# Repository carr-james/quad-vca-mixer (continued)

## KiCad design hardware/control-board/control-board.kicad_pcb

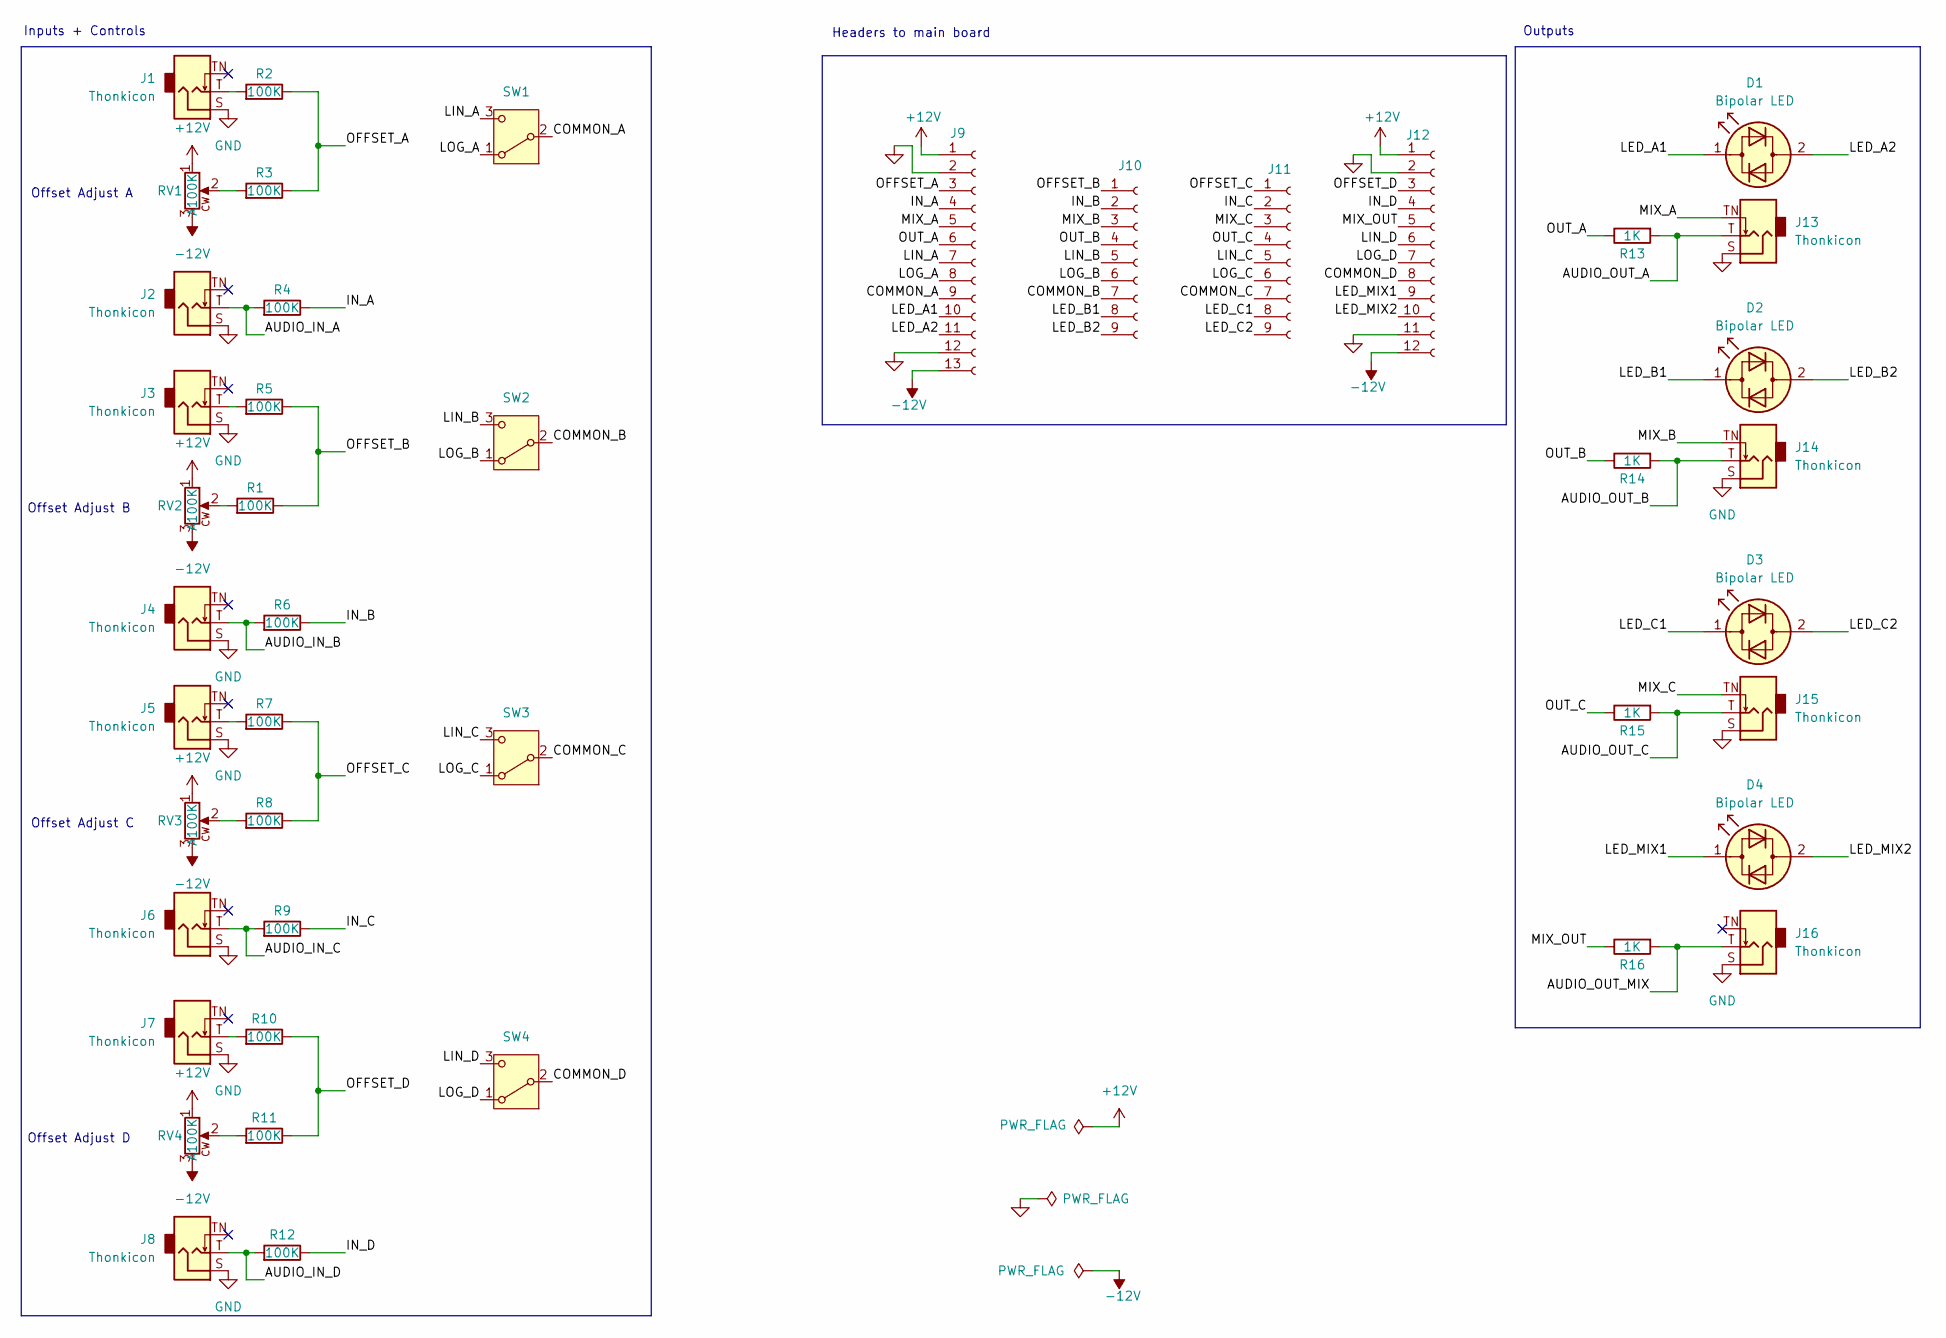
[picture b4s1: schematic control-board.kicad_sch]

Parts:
D1, D2, D3, D4: Bipolar LED; LED_D3.0mm
J1, J2, J3, J4, J5, J6, J7, J8, J13, J14, J15, J16: Thonkicon
J9: 01x13 Male Pin Header; PinHeader_1x13_P2.54mm_Vertical
J10, J11: 01x09 Male Pin Header; PinHeader_1x09_P2.54mm_Vertical
J12: 01x12 Male Pin Header; PinHeader_1x12_P2.54mm_Vertical
R1, R2, R3, R4, R5, R6, R7, R8, R9, R10, R11, R12: 100K; R_Axial_DIN0207_L6.3mm_D2.5mm_P7.62mm_Horizontal
R13, R14, R15, R16: 1K; R_Axial_DIN0207_L6.3mm_D2.5mm_P7.62mm_Horizontal
RV1, RV2, RV3, RV4: A100K; Alpha Potentiometer
SW1, SW2, SW3, SW4: Subminiture SPDT; Sub-Miniature SPDT

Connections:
+12V: J9.1, J12.1, RV1.1, RV2.1, RV3.1, RV4.1
-12V: J9.13, J12.12, RV1.3, RV2.3, RV3.3, RV4.3
/AUDIO_IN_A: J2.T, R4.1
/AUDIO_IN_B: J4.T, R6.1
/AUDIO_IN_C: J6.T, R9.1
/AUDIO_IN_D: J8.T, R12.1
/AUDIO_OUT_A: J13.T, R13.1
/AUDIO_OUT_B: J14.T, R14.1
/AUDIO_OUT_C: J15.T, R15.1
/AUDIO_OUT_MIX: J16.T, R16.1
/COMMON_A: J9.9, SW1.2 (B)
/COMMON_B: J10.7, SW2.2 (B)
/COMMON_C: J11.7, SW3.2 (B)
/COMMON_D: J12.8, SW4.2 (B)
/IN_A: J9.4, R4.2
/IN_B: J10.2, R6.2
/IN_C: J11.2, R9.2
/IN_D: J12.4, R12.2
/LED_A1: D1.1 (KA), J9.10
/LED_A2: D1.2 (AK), J9.11
/LED_B1: D2.1 (KA), J10.8
/LED_B2: D2.2 (AK), J10.9
/LED_C1: D3.1 (KA), J11.8
/LED_C2: D3.2 (AK), J11.9
/LED_MIX1: D4.1 (KA), J12.9
/LED_MIX2: D4.2 (AK), J12.10
/LIN_A: J9.7, SW1.3 (C)
/LIN_B: J10.5, SW2.3 (C)
/LIN_C: J11.5, SW3.3 (C)
/LIN_D: J12.6, SW4.3 (C)
/LOG_A: J9.8, SW1.1 (A)
/LOG_B: J10.6, SW2.1 (A)
/LOG_C: J11.6, SW3.1 (A)
/LOG_D: J12.7, SW4.1 (A)
/MIX_A: J9.5, J13.TN
/MIX_B: J10.3, J14.TN
/MIX_C: J11.3, J15.TN
/MIX_OUT: J12.5, R16.2
/OFFSET_A: J9.3, R2.2, R3.2
/OFFSET_B: J10.1, R1.2, R5.2
/OFFSET_C: J11.1, R7.2, R8.2
/OFFSET_D: J12.3, R10.2, R11.2
/OUT_A: J9.6, R13.2
/OUT_B: J10.4, R14.2
/OUT_C: J11.4, R15.2
GND: J1.S, J2.S, J3.S, J4.S, J5.S, J6.S, J7.S, J8.S, J9.2, J9.12, J12.2, J12.11, J13.S, J14.S, J15.S, J16.S
unnamed: J1.T, R2.1
unnamed: J3.T, R5.1
unnamed: J5.T, R7.1
unnamed: J7.T, R10.1
unnamed: R1.1, RV2.2
unnamed: R3.1, RV1.2
unnamed: R8.1, RV3.2
unnamed: R11.1, RV4.2

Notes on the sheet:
Offset Adjust D
Outputs
Offset Adjust C
Offset Adjust B
Offset Adjust A
Headers to main board
Inputs + Controls

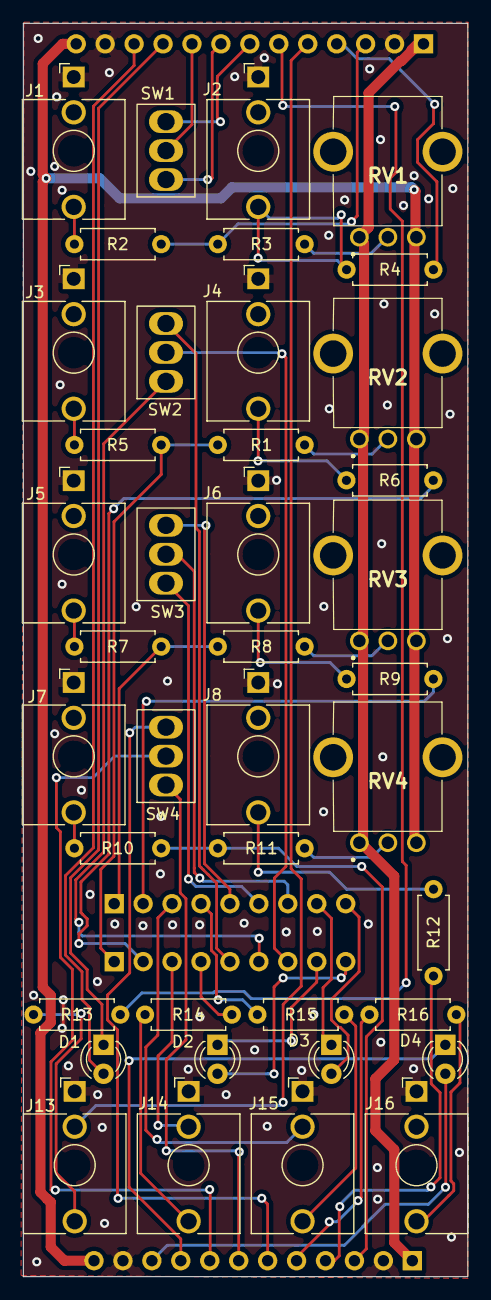
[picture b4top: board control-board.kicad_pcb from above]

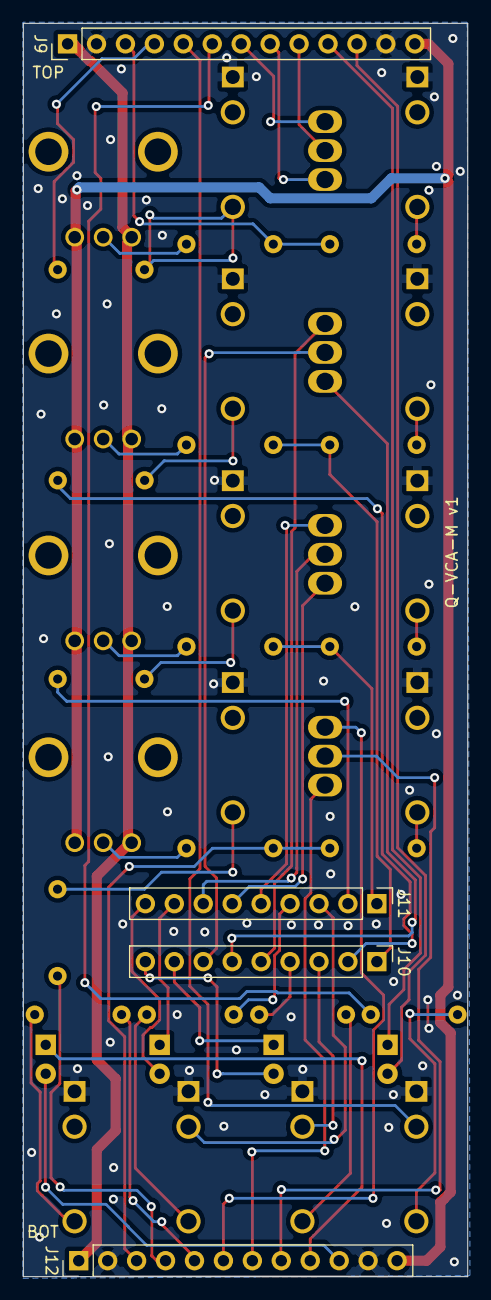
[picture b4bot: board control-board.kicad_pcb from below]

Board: 2 copper layers, 39.0 x 110.0 mm, 44 parts (4 on the bottom side), 54 nets.

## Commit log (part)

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2025-11-02 control and middle board complete
2025-11-02 chore: Add hardware/shared as submodule
2025-11-02 wip - first pass done
2025-11-02 chore: shared release workflow
2025-11-02 chore: dev branch build
2025-11-03 chore: clean up the boards
2025-11-03 chore: add description and data sheet to ibom
2025-11-04 feature: front panel
2025-11-04 fix: add write permissions for release build
2025-11-05 feature: docs
2025-11-07 docs: add collector-cache-extension to antora
2025-11-10 chore: update to eurorack-docs-ui@1.5.0
2025-11-11 feature: optional DIP footprint on PCB for TL0X4 op amps
2025-11-16 fix: use https for submodules
2025-12-14 fix: inverted power pins on op amps
